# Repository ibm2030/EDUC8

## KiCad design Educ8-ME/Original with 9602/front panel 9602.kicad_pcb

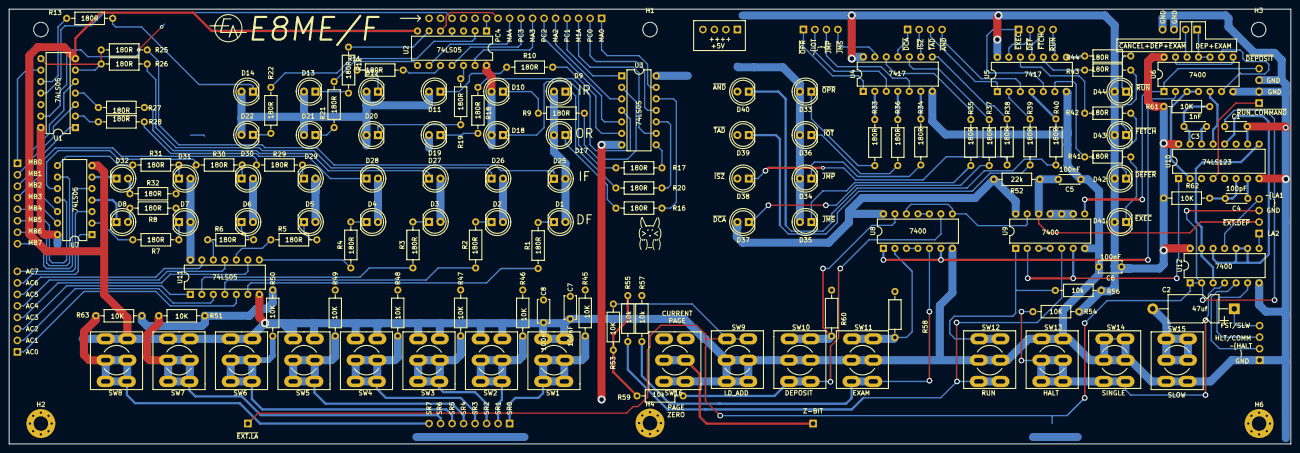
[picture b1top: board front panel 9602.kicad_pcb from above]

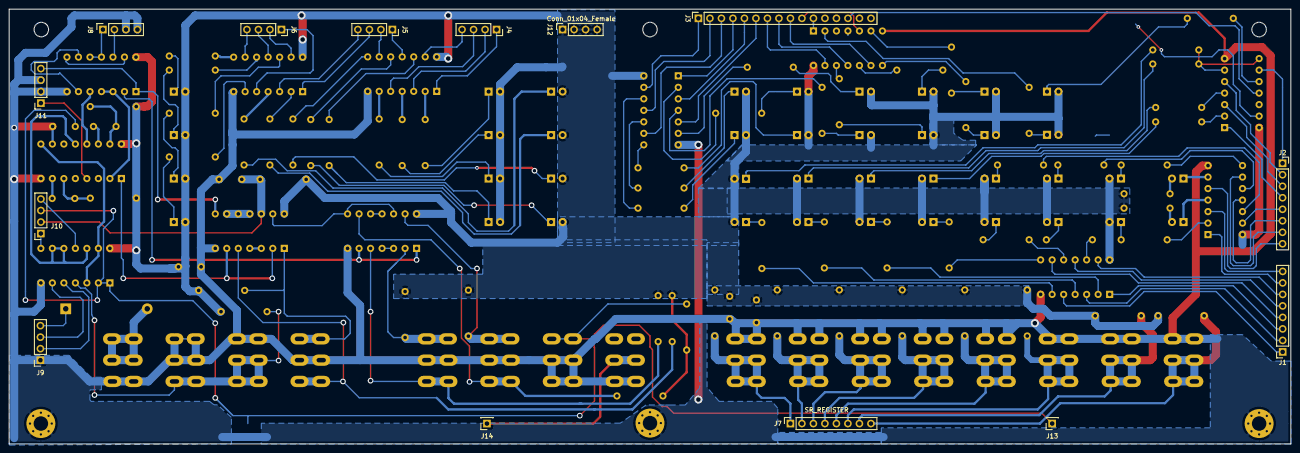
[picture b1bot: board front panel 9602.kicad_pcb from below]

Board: 2 copper layers, 283.0 x 96.0 mm, 155 parts (14 on the bottom side), 169 nets.

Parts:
C1, C5: 100nF; C_Disc_D4.3mm_W1.9mm_P5.00mm
C2: 47uf; CP_Axial_L11.0mm_D6.0mm_P18.00mm_Horizontal
C3: 1nF; C_Disc_D4.3mm_W1.9mm_P5.00mm
C4: 100pF; C_Disc_D4.3mm_W1.9mm_P5.00mm
C6, C7, C8: 100nF; C_Disc_D5.0mm_W2.5mm_P5.00mm
D1: AC0; LED_D5.0mm
D2: AC1; LED_D5.0mm
D3: AC2; LED_D5.0mm
D4: AC3; LED_D5.0mm
D5: AC4; LED_D5.0mm
D6: AC5; LED_D5.0mm
D7: AC6; LED_D5.0mm
D8: AC7; LED_D5.0mm
D9: PC0; LED_D5.0mm
D10: PC1; LED_D5.0mm
D11: PC2; LED_D5.0mm
D12: PC3; LED_D5.0mm
D13: PC4; LED_D5.0mm
D14: PC5; LED_D5.0mm
D17: MA0; LED_D5.0mm
D18: MA1; LED_D5.0mm
D19: MA2; LED_D5.0mm
D20: MA3; LED_D5.0mm
D21: MA4; LED_D5.0mm
D22: MA5; LED_D5.0mm
D25: MB0; LED_D5.0mm
D26: MB1; LED_D5.0mm
D27: MB2; LED_D5.0mm
D28: MB3; LED_D5.0mm
D29: MB4; LED_D5.0mm
D30: MB5; LED_D5.0mm
D31: MB6; LED_D5.0mm
D32: MB7; LED_D5.0mm
D33: ~{OPR}; LED_D5.0mm
D34: ~{JMP}; LED_D5.0mm
D35: ~{JMS}; LED_D5.0mm
D36: ~{IOT}; LED_D5.0mm
D37: ~{DCA}; LED_D5.0mm
D38: ~{ISZ}; LED_D5.0mm
D39: ~{TAD}; LED_D5.0mm
D40: ~{AND}; LED_D5.0mm
D41: ~{EXEC}; LED_D5.0mm
D42: ~{DEFER}; LED_D5.0mm
D43: ~{FETCH}; LED_D5.0mm
D44: ~{RUN}; LED_D5.0mm
H1, H3, H5: MountingHole; MountingHole_3.2mm_M3
H2, H4, H6: MountingHole_Pad; MountingHole_3.2mm_M3_Pad_Via
J1: Accumulator; PinSocket_1x08_P2.54mm_Vertical
J2: Mem_Buffer; PinSocket_1x08_P2.54mm_Vertical
J3: Conn_01x16_Female; PinSocket_1x16_P2.54mm_Vertical
J4, J5, J6, J8, J9, J10, J11, J12: Conn_01x04_Female; PinSocket_1x04_P2.54mm_Vertical
J7: SR_REGISTER; PinSocket_1x08_P2.54mm_Vertical
J13: ~{EXT.LA}; PinSocket_1x01_P2.54mm_Vertical
J14: Z-BIT; PinSocket_1x01_P2.54mm_Vertical
R1, R2, R3, R4, R5, R6, R7, R8, R9, R10, R11, R12, R13, R16, R17, R18, R19, R20, R21, R22, R25, R26, R27, R28, R29, R30, R31, R32, R33, R34, R35, R36, R37, R38, R39, R40, R41, R42, R43, R44: 180R; R_Axial_DIN0207_L6.3mm_D2.5mm_P10.16mm_Horizontal
R45, R46, R47, R48, R49, R50, R51, R53, R54, R61, R62, R63: 10K; R_Axial_DIN0207_L6.3mm_D2.5mm_P10.16mm_Horizontal
R52: 22k; R_Axial_DIN0207_L6.3mm_D2.5mm_P10.16mm_Horizontal
R55, R56, R57, R58, R59, R60: 10k; R_Axial_DIN0207_L6.3mm_D2.5mm_P10.16mm_Horizontal
SW1: SR0; DPDT_toggle_switch_wired
SW2: SR1; DPDT_toggle_switch_wired
SW3: SR2; DPDT_toggle_switch_wired
SW4: SR3; DPDT_toggle_switch_wired
SW5: SR4; DPDT_toggle_switch_wired
SW6: SR5; DPDT_toggle_switch_wired
SW7: SR6; DPDT_toggle_switch_wired
SW8: SR7; DPDT_toggle_switch_wired
SW9: LD_ADD; DPDT_toggle_switch_wired
SW10: DEPOSIT; DPDT_toggle_switch_wired
SW11: EXAM; DPDT_toggle_switch_wired
SW12: RUN; DPDT_toggle_switch_wired
SW13: HALT; DPDT_toggle_switch_wired
SW14: SINGLE; DPDT_toggle_switch_wired
SW15, SW16: SLOW; DPDT_toggle_switch_wired
U1, U2, U3, U7, U11: 74LS05; DIP-14_W7.62mm
U4, U5: 7417; DIP-14_W7.62mm
U6, U8, U9, U12: 7400; DIP-14_W7.62mm
U10: 74LS123; DIP-16_W7.62mm

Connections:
+5V: C6.1, C7.1, C8.1, D1.2, D2.2, D3.2, D4.2, D5.2, D6.2, D7.2, D9.2, D10.2, D11.2, D12.2, D13.2, D14.2, D17.2, D18.2, D19.2, D20.2, D21.2, D22.2, D25.2, D26.2, D27.2, D28.2, D29.2, D30.2, D31.2, D33.2, D34.2, D35.2, D36.2, D37.2, D38.2, D39.2, D40.2, D41.2, D42.2, D43.2, D44.2, J12.1, J12.2, J12.3, J12.4, R8.2, R32.2, R45.2, R46.2, R47.2, R48.2, R49.2, R50.2, R51.2, R52.1, R53.2, R54.2, R55.2, R56.1, R57.2, R58.1, R59.2, R60.1, R61.1, R62.1, R63.2, U1.14, U2.14, U3.14, U4.14, U5.14, U6.14, U7.14, U8.14, U9.14, U10.16, U11.14, U12.14
AC0: J1.1, U11.5
AC1: J1.2, U11.3
AC2: J1.3, U11.1
AC3: J1.4, U11.9
AC4: J1.5, U11.11
AC5: J1.6, U11.13
AC6: J1.7, U7.1
AC7: J1.8, U7.3
FAST_SLOW: C2.1, J9.4
GND: C1.2, C5.1, C6.2, C7.2, C8.2, H2.1, H4.1, H6.1, J8.3, J8.4, J9.1, J11.2, J11.3, SW1.1, SW1.4, SW2.1, SW2.4, SW3.1, SW3.4, SW4.1, SW4.4, SW5.1, SW5.4, SW6.1, SW6.4, SW7.1, SW7.4, SW8.1, SW8.4, SW9.1, SW9.2, SW9.4, SW9.5, SW10.2, SW10.5, SW11.2, SW11.5, SW12.2, SW12.5, SW13.3, SW13.6, SW14.2, SW14.3, SW14.5, SW14.6, SW15.3, SW15.6, SW16.3, SW16.6, U1.7, U2.7, U3.7, U4.7, U5.7, U6.7, U7.7, U8.7, U9.7, U10.8, U10.10, U11.7, U12.7
HLT_COMM: J9.3, U12.6
LA2: J10.1, U12.8
MA0: J3.1, U3.13
MA1: J3.3, U3.9
MA2: J3.5, U3.3
MA3: J3.7, U2.13
MA4: J3.9, U2.9
MA5: J3.11, U2.1
MA6: J3.12, U2.3
MB0: J2.1, U1.9
MB1: J2.2, U1.5
MB2: J2.3, U1.3
MB3: J2.4, U1.1
MB4: J2.5, U7.13
MB5: J2.6, U7.11
MB6: J2.7, U7.9
MB7: J2.8, U7.5
unnamed: C2.2, SW15.1, SW15.2, SW15.4, SW15.5
unnamed: C3.1, U10.14
unnamed: C3.2, R61.2, U10.15
unnamed: C4.1, U10.7
unnamed: C4.2, R62.2, U10.6
unnamed: D1.1, R1.2
unnamed: D2.1, R2.2
unnamed: D3.1, R3.2
unnamed: D4.1, R4.2
unnamed: D5.1, R5.2
unnamed: D6.1, R6.2
unnamed: D7.1, R7.2
unnamed: D8.1, U7.4
unnamed: D8.2, R8.1
unnamed: D9.1, R20.2
unnamed: D10.1, R9.2
unnamed: D11.1, R10.2
unnamed: D12.1, R11.2
unnamed: D13.1, R12.2
unnamed: D14.1, R13.2
unnamed: D17.1, R16.2
unnamed: D18.1, R17.2
unnamed: D19.1, R18.2
unnamed: D20.1, R19.2
unnamed: D21.1, R21.2
unnamed: D22.1, R22.2
unnamed: D25.1, R25.2
unnamed: D26.1, R26.2
unnamed: D27.1, R27.2
unnamed: D28.1, R28.2
unnamed: D29.1, R29.2
unnamed: D30.1, R30.2
unnamed: D31.1, R31.2
unnamed: D32.1, U7.6
unnamed: D32.2, R32.1
unnamed: D33.1, R33.2
unnamed: D34.1, R34.2
unnamed: D35.1, R35.2
unnamed: D36.1, R36.2
unnamed: D37.1, R37.2
unnamed: D38.1, R38.2
unnamed: D39.1, R39.2
unnamed: D40.1, R40.2
unnamed: D41.1, R41.2
unnamed: D42.1, R42.2
unnamed: D43.1, R43.2
unnamed: D44.1, R44.2
unnamed: J14.1, SW16.2, SW16.5
unnamed: R1.1, U11.6
unnamed: R2.1, U11.4
unnamed: R3.1, U11.2
unnamed: R4.1, U11.8
unnamed: R5.1, U11.10
unnamed: R6.1, U11.12
unnamed: R7.1, U7.2
unnamed: R9.1, U3.2
unnamed: R10.1, U3.6
unnamed: R11.1, U2.10
unnamed: R12.1, U2.6
unnamed: R13.1, U1.10
unnamed: R16.1, U3.12
unnamed: R17.1, U3.8
unnamed: R18.1, U3.4
unnamed: R19.1, U2.12
unnamed: R20.1, U3.10
unnamed: R21.1, U2.8
unnamed: R22.1, U2.2
unnamed: R25.1, U1.8
unnamed: R26.1, U1.6
unnamed: R27.1, U1.4
unnamed: R28.1, U1.2
unnamed: R29.1, U7.12
unnamed: R30.1, U7.10
unnamed: R31.1, U7.8
unnamed: R33.1, U4.2
unnamed: R34.1, U4.6
unnamed: R35.1, U4.12
unnamed: R36.1, U4.4
unnamed: R37.1, U4.10
unnamed: R38.1, U4.8
unnamed: R39.1, U5.2
unnamed: R40.1, U5.4
unnamed: R41.1, U5.6
unnamed: R42.1, U5.12
unnamed: R43.1, U5.10
unnamed: R44.1, U5.8
unnamed: R54.1, SW13.1, SW13.2, SW13.4, SW13.5, SW14.1, SW14.4, U12.4
unnamed: R55.1, SW12.1, SW12.4, U9.5
unnamed: R56.2, SW12.3, SW12.6, U9.1
unnamed: R57.1, SW11.1, SW11.4, U8.5
unnamed: R58.2, SW11.3, SW11.6, U8.2
unnamed: R59.1, SW10.1, SW10.4, U8.9
unnamed: R60.2, SW10.3, SW10.6, U8.13
unnamed: U6.2, U8.1, U8.6
unnamed: U6.6, U6.9
unnamed: U6.8, U6.13
unnamed: U8.3, U8.4
unnamed: U8.10, U8.11
unnamed: U8.8, U8.12, U9.13
unnamed: U9.3, U9.4
unnamed: U9.9, U9.10, U9.11
unnamed: U9.2, U9.6, U10.1
unnamed: U6.3, U6.4, U10.2
unnamed: U10.9, U12.3, U12.13
unnamed: U10.12, U12.9, U12.10, U12.12
unnamed: U6.5, U10.13
PC0: J3.2, U3.11
PC1: J3.4, U3.1
PC2: J3.6, U3.5
PC3: J3.8, U2.11
PC4: J3.10, U2.5
PC5: J3.14, U1.11
PC6: J3.15, U1.13
SR0: J7.1, R45.1, SW1.2, SW1.3, SW1.5, SW1.6
SR1: J7.2, R46.1, SW2.2, SW2.3, SW2.5, SW2.6
SR2: J7.3, R47.1, SW3.2, SW3.3, SW3.5, SW3.6
SR3: J7.4, R48.1, SW4.2, SW4.3, SW4.5, SW4.6
SR4: J7.5, R49.1, SW5.2, SW5.3, SW5.5, SW5.6
SR5: J7.6, R50.1, SW6.2, SW6.3, SW6.5, SW6.6
SR6: J7.7, R51.1, SW7.2, SW7.3, SW7.5, SW7.6
SR7: J7.8, R63.1, SW8.2, SW8.3, SW8.5, SW8.6
~AND: J5.4, U5.3
~CANCEL+DEP+EXAM: J8.2, U6.12
~DCA: J5.1, U4.11
~DEFER: J6.2, U5.13
~DEP+EXAM: J8.1, U6.10, U6.11
~DEPOSIT: J11.4, U6.1, U9.8
~EXEC: J6.1, U5.5
~EXT.DEPOSIT: C5.2, J10.2, R52.2, U9.12
~EXT.LA: C1.1, J10.3, J13.1, R53.1, SW9.3, SW9.6, U12.1, U12.2
~FETCH: J6.3, U5.11
~HLT: J9.2, U12.5
~IOT: J4.2, U4.3
~ISZ: J5.2, U4.9
~JMP: J4.3, U4.5
~JMS: J4.4, U4.13
~LA1: J10.4, U12.11
~OPR: J4.1, U4.1
~RUN_COMMAND: J11.1, U10.4
~RUN: J6.4, U5.9
~TAD: J5.3, U5.1

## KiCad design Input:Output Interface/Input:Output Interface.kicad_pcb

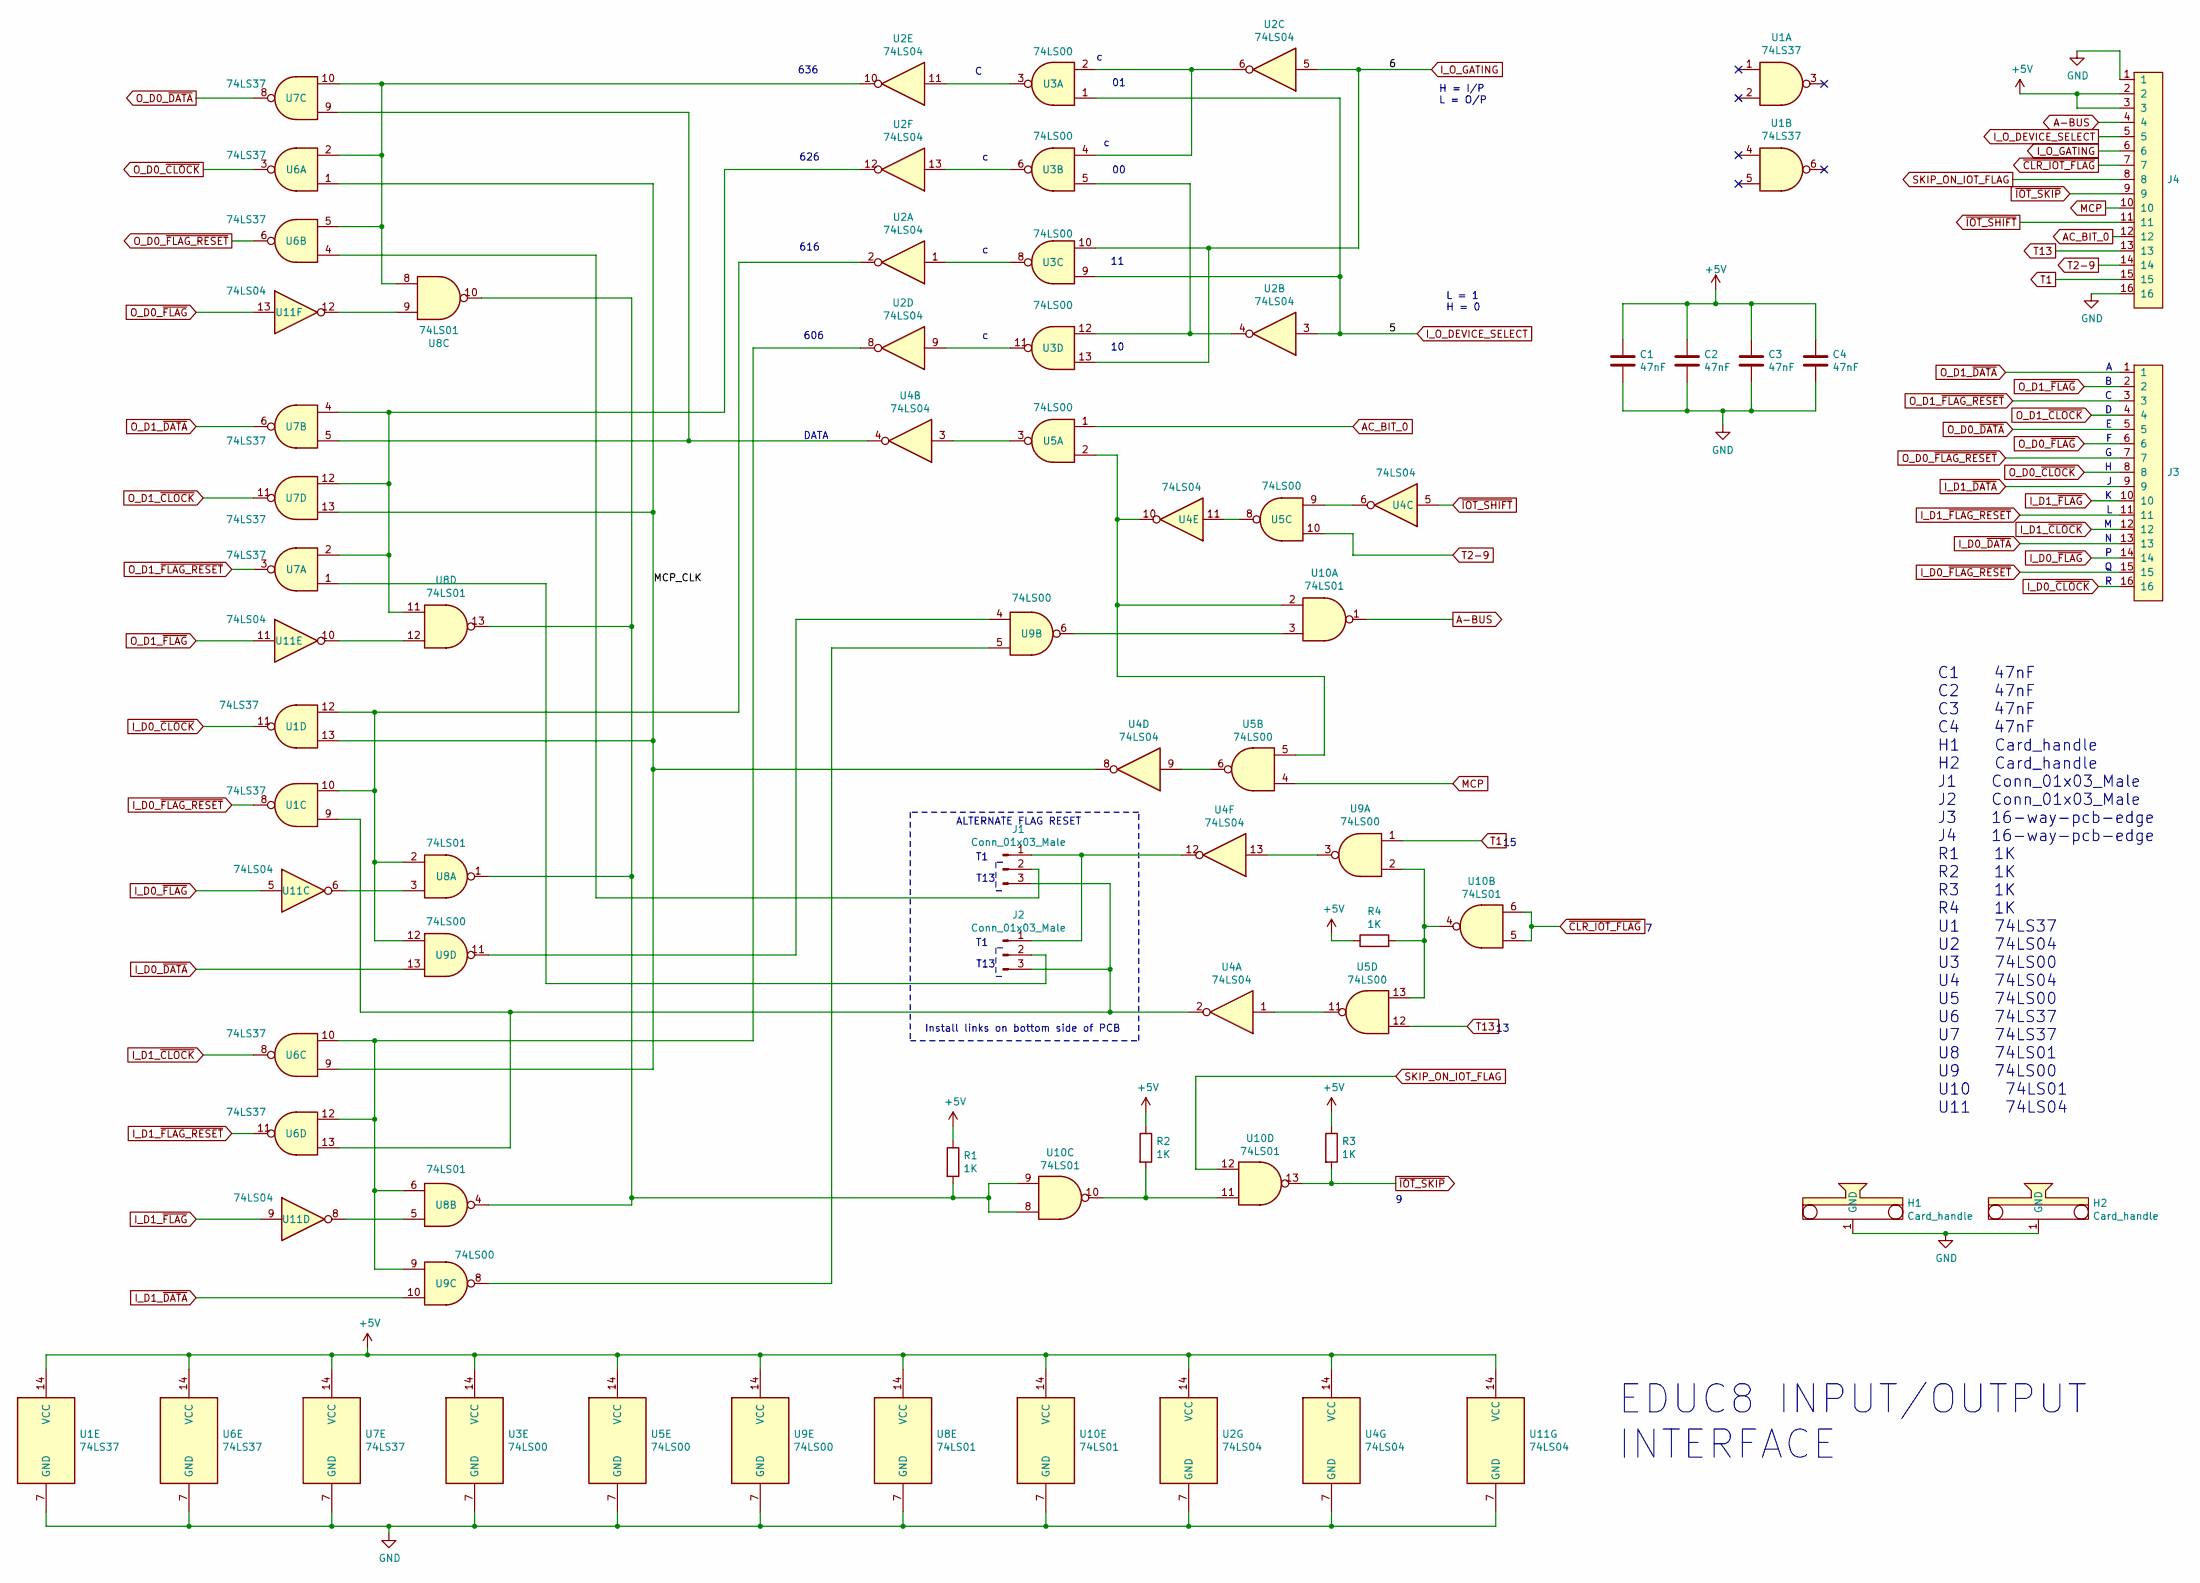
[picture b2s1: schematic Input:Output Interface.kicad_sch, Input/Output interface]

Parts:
C1, C2, C3, C4: 47nF; C_Disc_D7.5mm_W5.0mm_P7.50mm
H1, H2: Card_handle
J1, J2: Conn_01x03_Male; PinHeader_1x03_P2.54mm_Vertical
J3, J4: 16-way-pcb-edge-Educ-8-connectors; PCB_16pin
R1, R2, R3, R4: 1K; R_Axial_DIN0207_L6.3mm_D2.5mm_P10.16mm_Horizontal
U1, U6, U7: 74LS37; DIP-14_W7.62mm
U2, U4, U11: 74LS04; DIP-14_W7.62mm
U3: 74LS00
U5, U9: 74LS00; DIP-14_W7.62mm
U8, U10: 74LS01; DIP-14_W7.62mm

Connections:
+5V: C1.1, C2.1, C3.1, C4.1, J4.2, J4.3, R1.1, R2.1, R3.1, R4.1, U1.14 (VCC), U2.14 (VCC), U3.14 (VCC), U4.14 (VCC), U5.14 (VCC), U6.14 (VCC), U7.14 (VCC), U8.14 (VCC), U9.14 (VCC), U10.14 (VCC), U11.14 (VCC)
/MCP_CLK: U1.13, U4.8, U6.1, U6.9, U7.13
A-BUS: J4.4, U10.1
AC_BIT_0: J4.12, U5.1
GND: C1.2, C2.2, C3.2, C4.2, H1.1, H2.1, J4.1, J4.16, U1.7 (GND), U2.7 (GND), U3.7 (GND), U4.7 (GND), U5.7 (GND), U6.7 (GND), U7.7 (GND), U8.7 (GND), U9.7 (GND), U10.7 (GND), U11.7 (GND)
I_D0_~CLOCK: J3.16, U1.11
I_D0_~DATA: J3.13, U9.13
I_D0_~FLAG_RESET: J3.15, U1.8
I_D0_~FLAG: J3.14, U11.5
I_D1_~CLOCK: J3.12, U6.8
I_D1_~DATA: J3.9, U9.10
I_D1_~FLAG_RESET: J3.11, U6.11
I_D1_~FLAG: J3.10, U11.9
I_O_DEVICE_SELECT: J4.5, U2.3, U3.1, U3.9
I_O_GATING: J4.6, U2.5, U3.10, U3.13
MCP: J4.10, U5.4
unnamed: J1.1, J2.1, U4.12
unnamed: J1.2, U6.4
unnamed: J1.3, J2.3, U1.9, U4.2, U6.13
unnamed: J2.2, U7.1
unnamed: R1.2, U8.1, U8.4, U8.10, U8.13, U10.8, U10.9
unnamed: R2.2, U10.10, U10.11
unnamed: R4.2, U5.13, U9.2, U10.4
unnamed: U1.10, U1.12, U2.2, U8.2, U9.12
unnamed: U2.1, U3.8
unnamed: U2.4, U3.5, U3.12
unnamed: U2.6, U3.2, U3.4
unnamed: U2.8, U6.10, U6.12, U8.6, U9.9
unnamed: U2.9, U3.11
unnamed: U2.10, U6.2, U6.5, U7.10, U8.8
unnamed: U2.11, U3.3
unnamed: U2.12, U7.2, U7.4, U7.12, U8.11
unnamed: U2.13, U3.6
unnamed: U4.1, U5.11
unnamed: U4.3, U5.3
unnamed: U4.4, U7.5, U7.9
unnamed: U4.6, U5.9
unnamed: U4.9, U5.6
unnamed: U4.11, U5.8
unnamed: U4.13, U9.3
unnamed: U9.5, U9.8
unnamed: U9.4, U9.11
unnamed: U4.10, U5.2, U5.5, U10.2
unnamed: U9.6, U10.3
unnamed: U8.3, U11.6
unnamed: U8.5, U11.8
unnamed: U8.12, U11.10
unnamed: U8.9, U11.12
O_D0_~CLOCK: J3.8, U6.3
O_D0_~DATA: J3.5, U7.8
O_D0_~FLAG_RESET: J3.7, U6.6
O_D0_~FLAG: J3.6, U11.13
O_D1_~CLOCK: J3.4, U7.11
O_D1_~DATA: J3.1, U7.6
O_D1_~FLAG_RESET: J3.3, U7.3
O_D1_~FLAG: J3.2, U11.11
SKIP_ON_IOT_FLAG: J4.8, U10.12
T1: J4.15, U9.1
T2-9: J4.14, U5.10
T13: J4.13, U5.12
~CLR_IOT_FLAG: J4.7, U10.5, U10.6
~IOT_SHIFT: J4.11, U4.5
~IOT_SKIP: J4.9, R3.2, U10.13

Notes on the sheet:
616
EDUC8 INPUT/OUTPUT INTERFACE
T13
H = I/P L = O/P
DATA
L = 1 H = 0
Install links on bottom side of PCB
636
626
606
C1 47nF C2 47nF C3 47nF C4 47nF H1 Card_handle H2 Card_handle J1 Conn_01x03_Male J2 Conn_01x03_Male J3 16-way-pcb-edge J4 16-way-pcb-edge R1 1K R2 1K R3 1K R4 1K U1 74LS37 U2 74LS04 U3 74LS00 U4 74LS04 U5 74LS00 U6 74LS37 U7 74LS37 U8 74LS01 U9 74LS00 U10 74LS01 U11 74LS04
ALTERNATE FLAG RESET

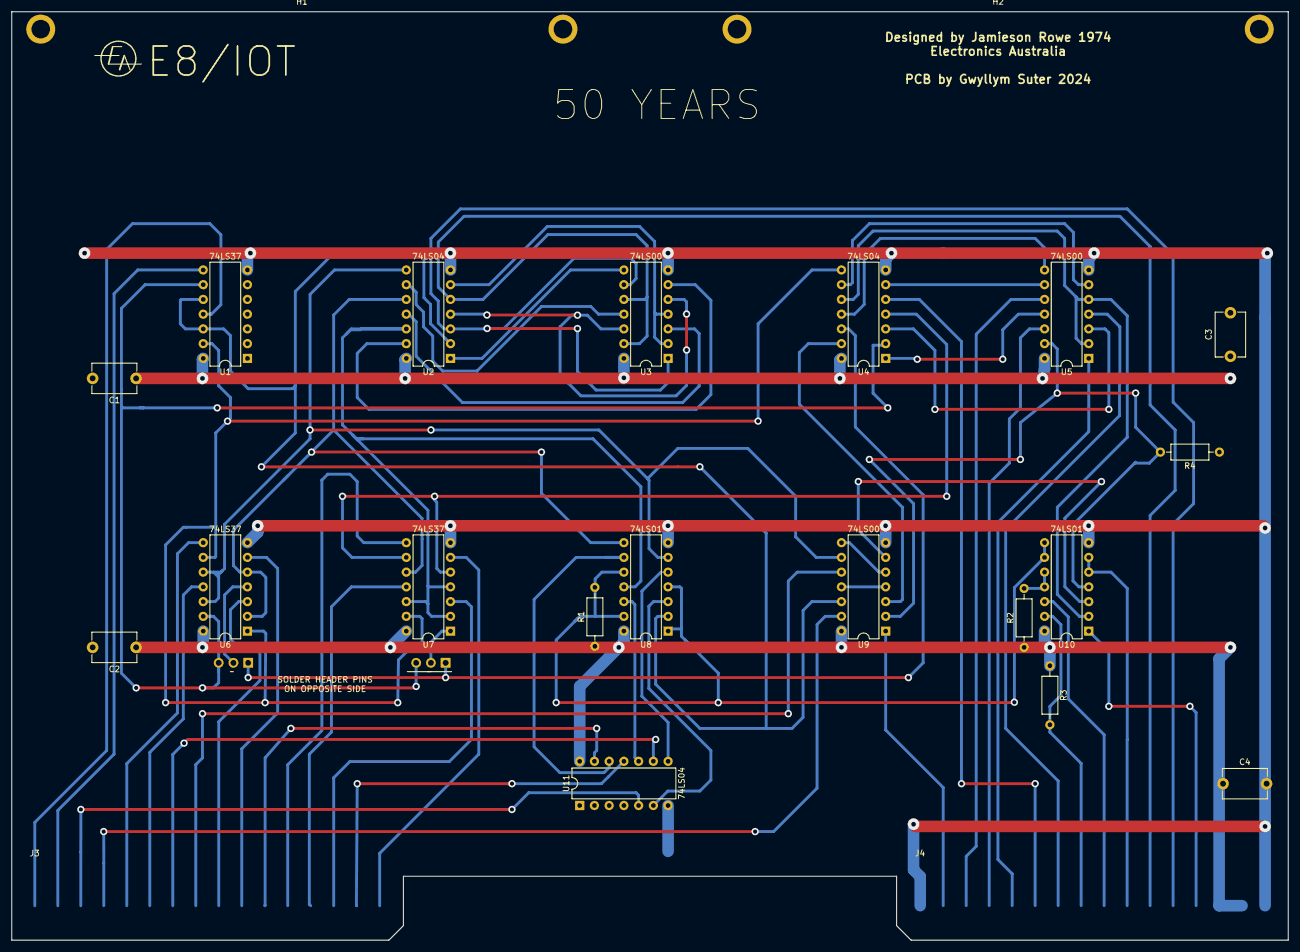
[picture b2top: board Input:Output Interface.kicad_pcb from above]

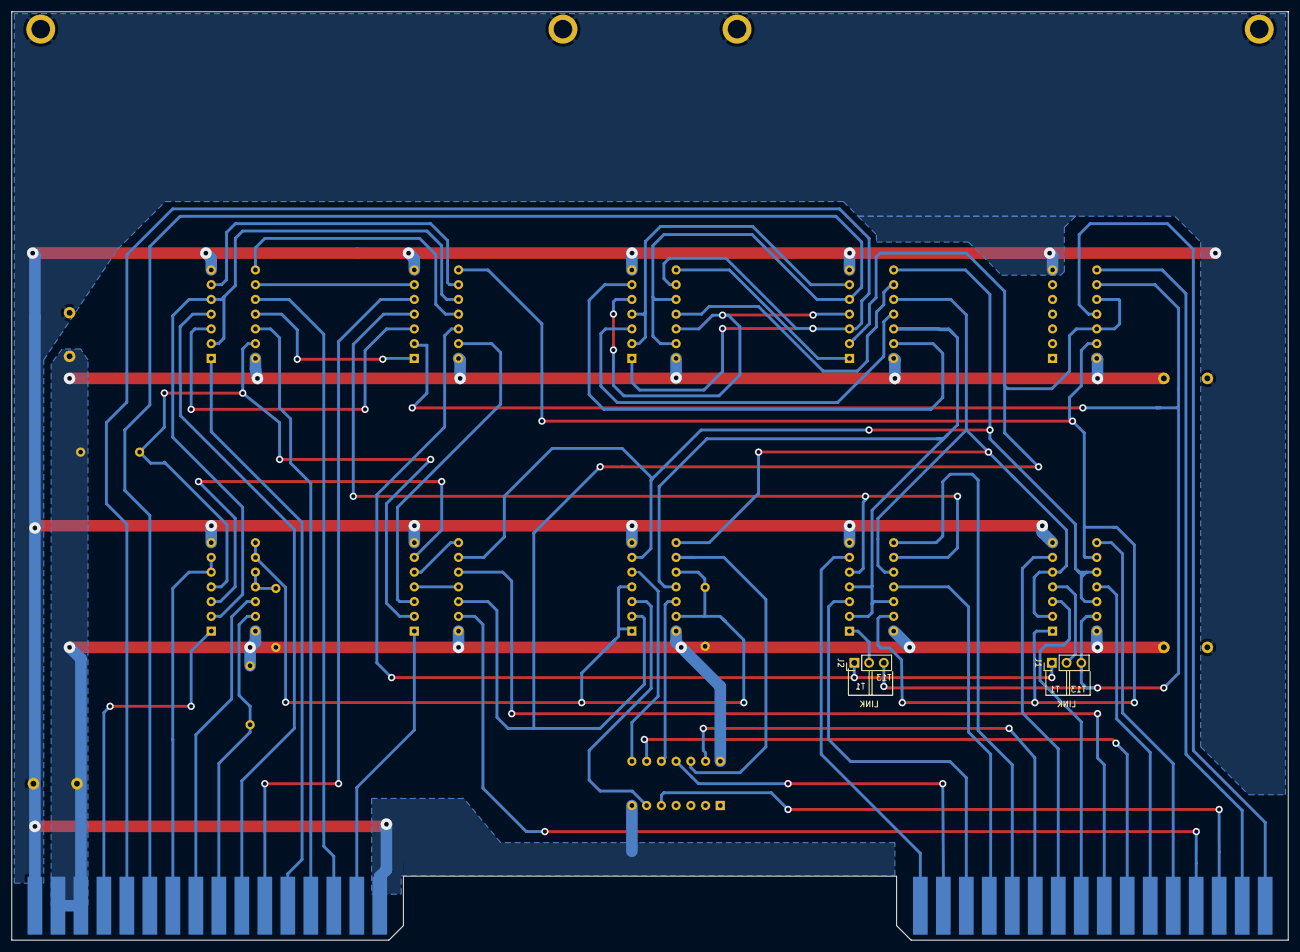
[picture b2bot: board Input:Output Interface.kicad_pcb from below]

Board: 2 copper layers, 220.0 x 160.0 mm, 25 parts (2 on the bottom side), 63 nets.

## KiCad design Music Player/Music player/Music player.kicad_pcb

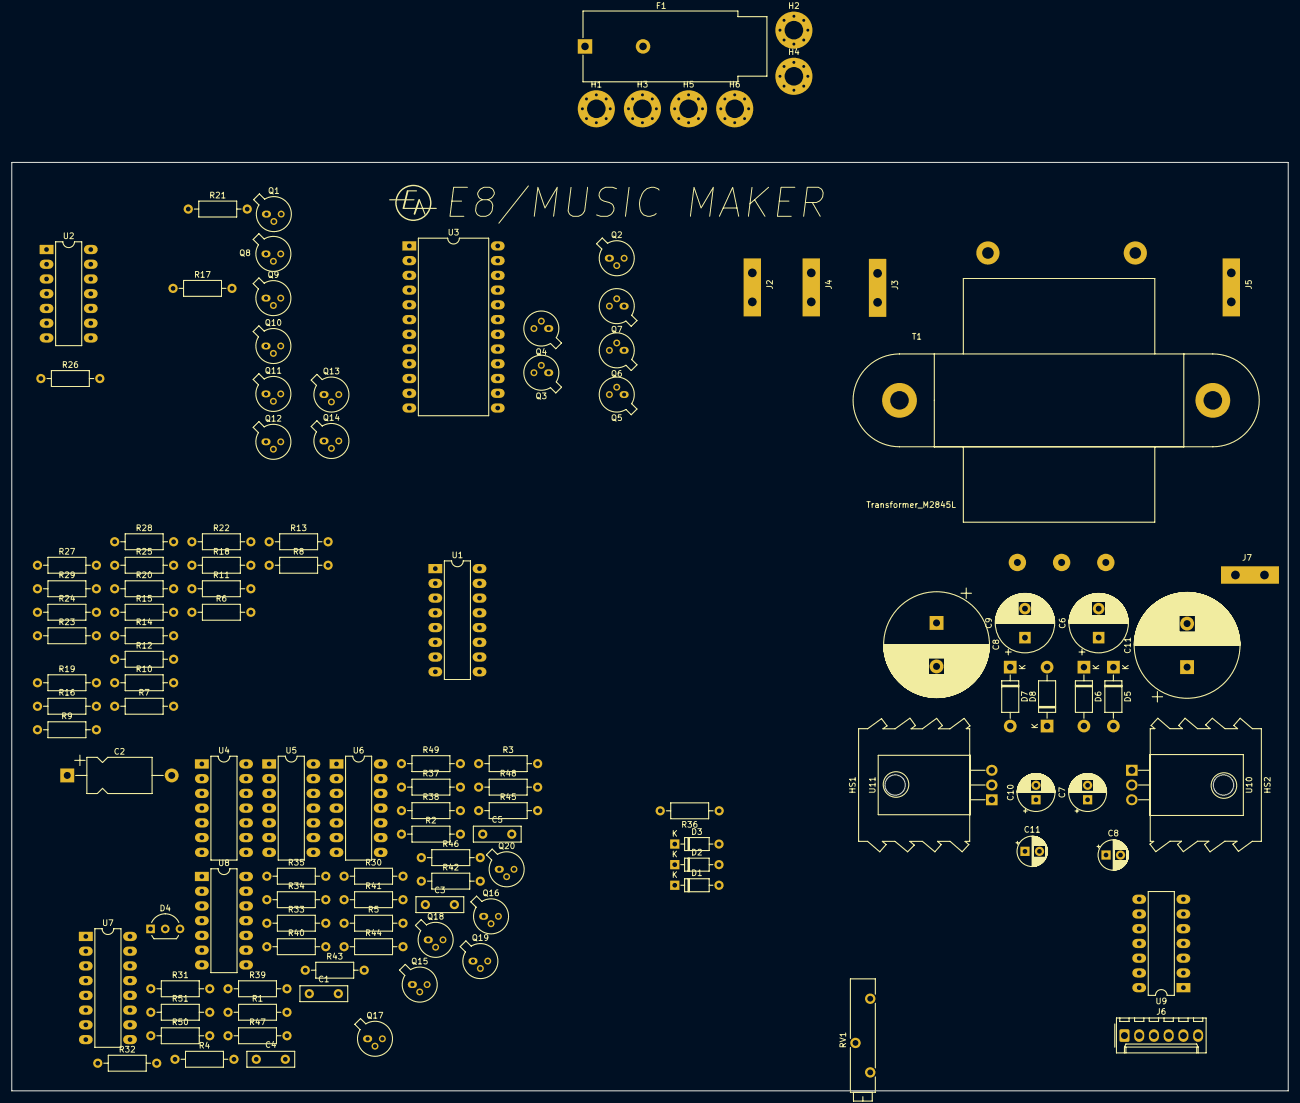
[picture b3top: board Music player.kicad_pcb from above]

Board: 2 copper layers, 220.0 x 160.0 mm, 120 parts (0 on the bottom side), 114 nets, no tracks yet.

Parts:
C1: 470pF; C_Disc_D8.0mm_W2.5mm_P5.00mm
C2: 47uF; CP_Axial_L11.0mm_D6.0mm_P18.00mm_Horizontal
C3: 10nF; C_Disc_D8.0mm_W2.5mm_P5.00mm
C4: 220nF; C_Disc_D8.0mm_W2.5mm_P5.00mm
C5: 1nf; C_Disc_D8.0mm_W2.5mm_P5.00mm
C6, C9: CP; CP_Radial_D10.0mm_P5.00mm
C7, C10: CP; CP_Radial_D6.3mm_P2.50mm
C8, C11: CP; CP_Radial_D18.0mm_P7.50mm
C8#2, C11#2: CP; CP_Radial_D5.0mm_P2.50mm
D1, D2, D3: 1N914; D_DO-35_SOD27_P7.62mm_Horizontal
D4: D13T1; TO-92L_Inline_Wide
D5, D6, D7, D8: 1N4001; D_DO-41_SOD81_P10.16mm_Horizontal
F1: Fuse; Fuseholder_Cylinder-5x20mm_Schurter_FAB_0031-355x_Horizonta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
H1, H2, H3, H4, H5, H6: MountingHole_Pad; MountingHole_3.2mm_M3_Pad_Via
HS1, HS2: Heatsink; Heatsink_Aavid-TV5G_TO220_Horizontal
J2, J3, J4: Active; QC_Terminal_PCB_W6.3mm_P5mm_
J5: Neutral; QC_Terminal_PCB_W6.3mm_P5mm_
J6: Conn_01x06_Male; Molex_KK-254_AE-6410-06A_1x06_P2.54mm_Vertical
J7: EARTH; QC_Terminal_PCB_W6.3mm_P5mm_
Q1, Q2, Q3, Q4, Q5, Q6, Q7, Q8, Q9, Q10, Q11, Q12, Q13, Q14, Q19, Q20: BC108; TO-18-3
Q15, Q16, Q17, Q18: 2N2906; TO-18-3
R1, R2, R36, R49: 2k2; R_Axial_DIN0207_L6.3mm_D2.5mm_P10.16mm_Horizontal
R3: 680R; R_Axial_DIN0207_L6.3mm_D2.5mm_P10.16mm_Horizontal
R4, R5, R30, R31, R50: 470R; R_Axial_DIN0207_L6.3mm_D2.5mm_P10.16mm_Horizontal
R6, R7, R8, R9, R10, R11, R18, R19, R20, R21, R22, R23: 10k; R_Axial_DIN0207_L6.3mm_D2.5mm_P10.16mm_Horizontal
R12, R13, R14, R15, R16, R17, R24, R25, R26, R27, R28, R29: 39k; R_Axial_DIN0207_L6.3mm_D2.5mm_P10.16mm_Horizontal
R32, R33, R34, R35, R46: 1k; R_Axial_DIN0207_L6.3mm_D2.5mm_P10.16mm_Horizontal
R37: 22k; R_Axial_DIN0207_L6.3mm_D2.5mm_P10.16mm_Horizontal
R38: 820k; R_Axial_DIN0207_L6.3mm_D2.5mm_P10.16mm_Horizontal
R39, R40, R47: 220K; R_Axial_DIN0207_L6.3mm_D2.5mm_P10.16mm_Horizontal
R41: 110k; R_Axial_DIN0207_L6.3mm_D2.5mm_P10.16mm_Horizontal
R42, R43, R44, R45: 4k7; R_Axial_DIN0207_L6.3mm_D2.5mm_P10.16mm_Horizontal
R48: 10R; R_Axial_DIN0207_L6.3mm_D2.5mm_P10.16mm_Horizontal
R51: R; R_Axial_DIN0207_L6.3mm_D2.5mm_P10.16mm_Horizontal
RV1: 25k; Potentiometer_Bourns_3005_Horizontal
T1: Transformer_M2845L; M2845L
U1: AY-1-0212; DIP-16_W7.62mm_LongPads
U2: 74LS13; DIP-14_W7.62mm_LongPads
U3: 74LS150; DIP-24_W15.24mm_LongPads
U4: 74LS93; DIP-14_W7.62mm_LongPads
U5: 74LS01; DIP-14_W7.62mm_LongPads
U6: 74LS04; DIP-14_W7.62mm_LongPads
U7: 74LS139; DIP-16_W7.62mm_LongPads
U8: 74LS164; DIP-14_W7.62mm_LongPads
U9: 74LS37; DIP-14_W7.62mm_LongPads
U10: L7812; TO-220F-3_Horizontal_TabDown
U11: LM7912_TO220; TO-220-3_Horizontal_TabDown

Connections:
+5V: J6.5, Q2.3, R1.1, R2.1, R6.1, R7.1, R8.1, R9.1, R10.1, R11.1, R18.1, R19.1, R20.1, R21.1, R22.1, R23.1, R30.1, U3.24, U4.5, U5.14, U6.14, U7.16, U8.14, U9.14
+12V: C7.1, C8#2.1, U1.1, U10.3
-12V: C10.2, C11#2.1, U1.9, U11.3
/Buffer/B0_1: Q3.3, R6.2, U3.19
/Buffer/B0_2: Q4.3, R7.2, U3.20
/Buffer/B0_3: Q5.3, R8.2, U3.21
/Buffer/B0_4: Q6.3, R9.2, U3.22
/Buffer/B0_5: Q7.3, R10.2, U3.23
/Buffer/B0_6: Q8.3, R11.2, U3.1
/Buffer/B0_7: Q9.3, R18.2, U3.2
/Buffer/B0_8: Q10.3, R19.2, U3.3
/Buffer/B0_9: Q11.3, R20.2, U3.4
/Buffer/B0_10: Q12.3, R21.2, U3.5
/Buffer/B0_12: Q13.3, R22.2, U3.6
/Buffer/B0_13: Q14.3, R23.2, U3.7
/Buffer/BI_1: R12.2, U1.8
/Buffer/BI_2: R13.2, U1.7
/Buffer/BI_3: R14.2, U1.11
/Buffer/BI_4: R15.2, U1.12
/Buffer/BI_5: R16.2, U1.6
/Buffer/BI_6: R17.2, U1.5
/Buffer/BI_7: R24.2, U1.13
/Buffer/BI_8: R25.2, U1.14
/Buffer/BI_9: R26.2, U1.4
/Buffer/BI_10: R27.2, U1.15
/Buffer/BI_11: R28.2, U1.16
/Buffer/BI_13: R29.2, U1.3
A0: U3.15, U8.13
A1: U3.14, U8.12
A2: U3.13, U8.11
A3: U3.11, U8.10
GND: C1.2, C3.2, C4.2, C7.2, C8.1, C8#2.2, C10.1, C11.2, C11#2.2, D4.3, D6.2, D8.1, J6.6, J7.1, Q1.1, Q3.1, Q4.1, Q5.1, Q6.1, Q7.1, Q8.1, Q9.1, Q10.1, Q11.1, Q12.1, Q13.1, Q14.1, R5.2, R31.2, R50.2, T1.0, T1.3, U1.10, U3.8, U3.12, U3.16, U3.17, U3.18, U4.2, U4.3, U4.10, U5.7, U6.7, U7.8, U8.7, U9.7, U10.2, U11.1
unnamed: C1.1, Q2.2, R4.2
unnamed: C2.1, R30.2, U5.1, U5.4, U5.10, U5.13
unnamed: C2.2, R46.1
unnamed: C3.1, R31.1, R46.2
unnamed: C4.1, Q19.2, R38.2, R40.2, R41.2, R47.2, R48.1
unnamed: C5.1, U2.6
unnamed: C5.2, R36.2, U9.5
unnamed: C6.1, D5.2, D6.1
unnamed: C6.2, C9.2, T1.5
unnamed: C8.2, D7.2, U11.2
unnamed: C9.1, D7.1, D8.2
unnamed: C11.1, D5.1, U10.1
unnamed: D1.1, D2.2
unnamed: D1.2, R36.1, R37.1
unnamed: D2.1, D3.2
unnamed: D3.1, Q15.1, Q16.1, Q17.1, Q18.1, R32.1, R33.1, R34.1, R35.1
unnamed: D4.1, R48.2
unnamed: D4.2, R37.2, R51.1
unnamed: F1.1, J2.1
unnamed: F1.2, J4.1
unnamed: H1.1, H2.1, H3.1, H4.1, H5.1, H6.1
unnamed: J3.1, T1.1
unnamed: J5.1, T1.2
unnamed: Q1.2, R3.1
unnamed: Q1.3, R2.2, U1.2
unnamed: Q2.1, R5.1, U2.13
unnamed: Q3.2, R12.1
unnamed: Q4.2, R13.1
unnamed: Q5.2, R14.1
unnamed: Q6.2, R15.1
unnamed: Q7.2, R16.1
unnamed: Q8.2, R17.1
unnamed: Q9.2, R24.1
unnamed: Q10.2, R25.1
unnamed: Q11.2, R26.1
unnamed: Q12.2, R27.1
unnamed: Q13.2, R28.1
unnamed: Q14.2, R29.1
unnamed: Q15.2, R32.2, R42.1
unnamed: Q15.3, R38.1
unnamed: Q16.2, R33.2, R43.1
unnamed: Q16.3, R39.1
unnamed: Q17.2, R34.2, R44.1
unnamed: Q17.3, R40.1
unnamed: Q18.2, R35.2, R45.1
unnamed: Q18.3, R41.1
unnamed: Q19.1, Q20.2
unnamed: Q19.3, Q20.3, R49.1
unnamed: Q20.1, R50.1, U2.1
unnamed: R1.2, U2.9, U2.10, U2.12
unnamed: R3.2, RV1.1, U2.8
unnamed: R4.1, RV1.2, RV1.3
unnamed: R39.2, R47.1
unnamed: R42.2, U7.7
unnamed: R43.2, U7.6
unnamed: R44.2, U7.5
unnamed: R45.2, U7.4
unnamed: R49.2, U2.2, U2.4, U2.5
unnamed: U3.10, U4.14
unnamed: U4.1, U4.12, U5.11
unnamed: U4.8, U5.5
unnamed: U4.9, U5.8
unnamed: U4.11, U5.2
unnamed: U5.3, U6.2
unnamed: U5.6, U6.4
unnamed: U5.9, U6.6
unnamed: U5.12, U6.8
unnamed: U6.1, U7.12
unnamed: U6.3, U7.11
unnamed: U6.5, U7.10
unnamed: U6.9, U7.9
unnamed: U7.1, U7.15, U9.2, U9.6, U9.9, U9.10
unnamed: U7.2, U8.4
unnamed: U7.3, U8.3
unnamed: U7.13, U8.5
unnamed: U7.14, U8.6
unnamed: U8.1, U8.2, U9.11
unnamed: U9.3, U9.4
~CLOCK: J6.4, U8.8
~DATA: J6.1, U9.12, U9.13
~FLAG: J6.2, U9.8
~RESET_FLAG: R51.2, U9.1
